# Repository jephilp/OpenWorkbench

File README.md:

# OpenWorkbench
A complete open source electrical prototyping and development toolkit. 

## The Idea
I'm currently a broke college student in Electrical Engineering. While I do have access to equipment that can meet my needs for projects, it's annoying to have to gain access to them every time I have to use them. Plus if I want to use them at home it will cost me many thousands of dollars which I don't have.

In comes the idea of the Open Workbench: I've begun gathering and developing equipment that will condense and simplify how prototyping can be done, without neededing to hunt around eBay, auctions, or buy cheap crappy equipment from Aliexpress. 

To get started I'm going to add my Logic Analyzer. It's built off of the Pi Pico Analyzer project but includes some things that I thought would be useful or nice. There's always room for improvement and I hope everyone will contribute.

## To Do:
- Create a list of basic BUILDABLE equipment.
- Create a list of BUYABLE equipment.
- Choose a mounting system (I'm thinking DIN rails).

## Current Projects:
- ATX Voltmeter
- Pi Logic Analyzer

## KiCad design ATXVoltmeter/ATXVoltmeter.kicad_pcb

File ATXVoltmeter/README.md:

# ATX VOLTMETER
Created to fufill the needs of most electrical prototyping needs. Still in progress
## Features
- +/-12 V, +/-5 V, +/-3.3 V, and Variable up to 30 V.
- Fuses on every rail
- Switches on every rail
- Current shunt on +/-12 V, +5 V and +3.3 V
- Integrated screen with monitoring

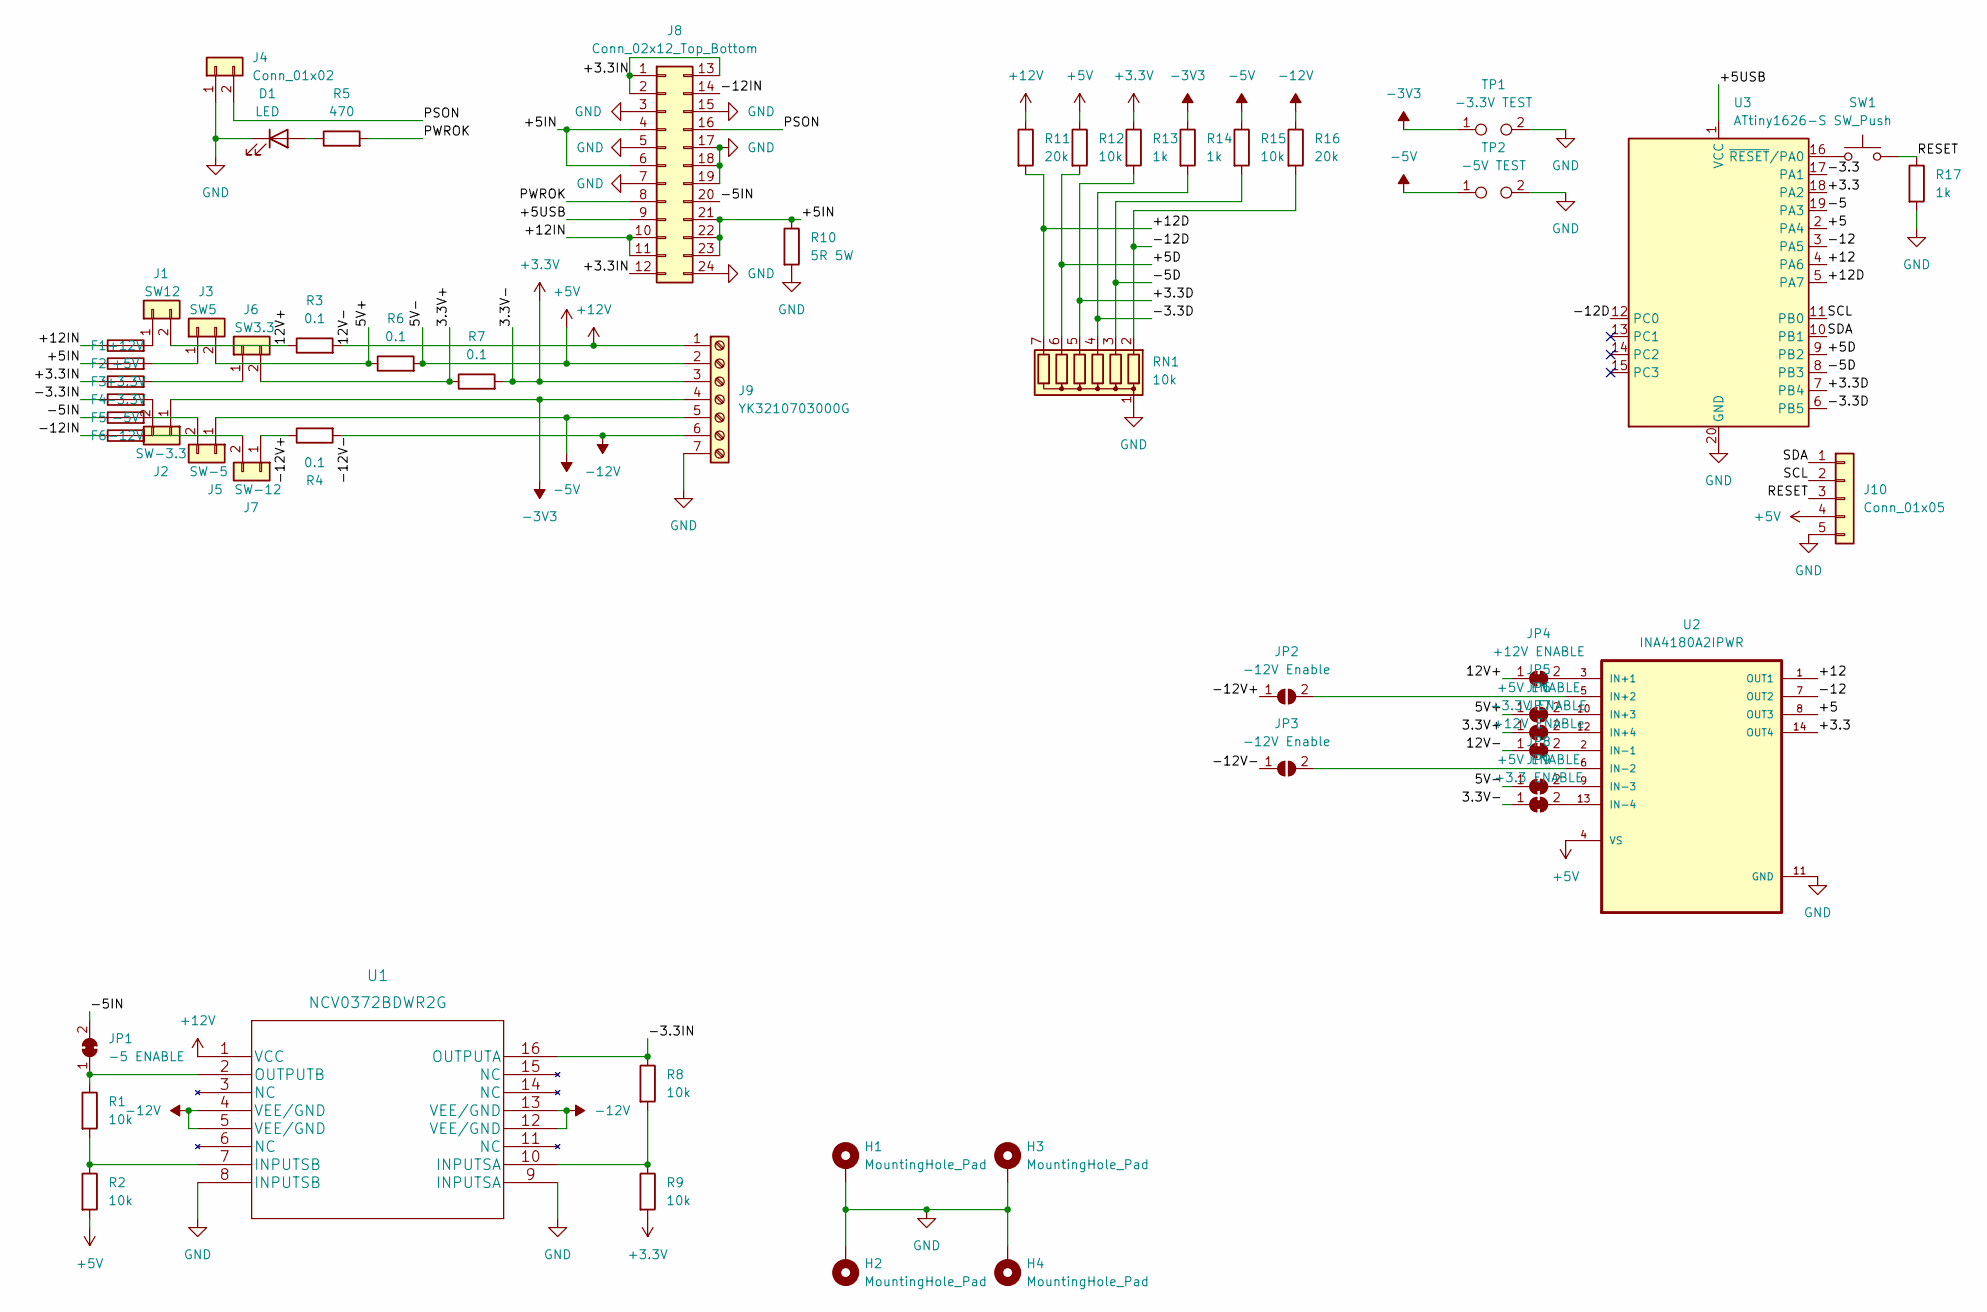
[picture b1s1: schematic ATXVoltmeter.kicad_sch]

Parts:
D1: LED; LED_D5.0mm
F1: +12V; Fuseholder_Blade_Mini_Keystone_3568
F2: +5V; Fuseholder_Blade_Mini_Keystone_3568
F3: +3.3V; Fuseholder_Blade_Mini_Keystone_3568
F4: -3.3V; Fuseholder_Blade_Mini_Keystone_3568
F5: -5V; Fuseholder_Blade_Mini_Keystone_3568
F6: -12V; Fuseholder_Blade_Mini_Keystone_3568
H1, H2, H3, H4: MountingHole_Pad; MountingHole_3.2mm_M3_DIN965_Pad
J1: SW12; AMASS_XT30U-F_1x02_P5.0mm_Vertical
J2: SW-3.3; AMASS_XT30U-F_1x02_P5.0mm_Vertical
J3: SW5; AMASS_XT30U-F_1x02_P5.0mm_Vertical
J4: Conn_01x02; PinHeader_1x02_P2.54mm_Vertical
J5: SW-5; AMASS_XT30U-F_1x02_P5.0mm_Vertical
J6: SW3.3; AMASS_XT30U-F_1x02_P5.0mm_Vertical
J7: SW-12; AMASS_XT30U-F_1x02_P5.0mm_Vertical
J8: Conn_02x12_Top_Bottom; Molex_Micro-Fit_3.0_43045-2412_2x12_P3.00mm_Vertical
J9: YK3210703000G; PhoenixContact_GMSTBVA_2,5_7-G-7,62_1x07_P7.62mm_Vertical
J10: Conn_01x05; PinSocket_1x05_P2.54mm_Horizontal
JP1: -5 ENABLE; SolderJumper-2_P1.3mm_Bridged_Pad1.0x1.5mm
JP2, JP3: -12V Enable; SolderJumper-2_P1.3mm_Open_Pad1.0x1.5mm
JP4: +12V ENABLE; SolderJumper-2_P1.3mm_Bridged_Pad1.0x1.5mm
JP5, JP8: +5V ENABLE; SolderJumper-2_P1.3mm_Bridged_Pad1.0x1.5mm
JP6: +3.3V ENABLE; SolderJumper-2_P1.3mm_Bridged_Pad1.0x1.5mm
JP7: +12V ENABLe; SolderJumper-2_P1.3mm_Bridged_Pad1.0x1.5mm
JP9: +3.3 ENABLE; SolderJumper-2_P1.3mm_Bridged_Pad1.0x1.5mm
R1, R2, R8, R9, R12, R15: 10k; R_Axial_DIN0207_L6.3mm_D2.5mm_P7.62mm_Horizontal
R3, R4, R6, R7: 0.1; R_Bare_Metal_Element_L16.3mm_W4.8mm_P15.30mm
R5: 470; R_Axial_DIN0207_L6.3mm_D2.5mm_P7.62mm_Horizontal
R10: 5R 5W; R_Axial_DIN0918_L18.0mm_D9.0mm_P22.86mm_Horizontal
R11, R16: 20k; R_Axial_DIN0207_L6.3mm_D2.5mm_P7.62mm_Horizontal
R13, R14, R17: 1k; R_Axial_DIN0207_L6.3mm_D2.5mm_P7.62mm_Horizontal
RN1: 10k; R_Array_SIP7
SW1: SW_Push; SW_PUSH_6mm
TP1: -3.3V TEST; TestPoint_2Pads_Pitch2.54mm_Drill0.8mm
TP2: -5V TEST; TestPoint_2Pads_Pitch2.54mm_Drill0.8mm
U1: NCV0372BDWR2G
U2: INA4180A2IPWR; SOP65P640X120-14N
U3: ATtiny1626-S; SOIC-20W_7.5x12.8mm_P1.27mm

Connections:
+3.3V: J9.3, JP9.1 (A), R7.2, R9.2, R13.1
+5V: J9.2, J10.4, JP8.1 (A), R2.2, R6.2, R12.1, U2.4 (VS)
+12V: J9.1, JP7.1 (A), R3.2, R11.1, U1.1 (VCC)
-3V3: J2.1, J9.4, R14.1, TP1.1
-5V: J5.1, J9.5, R15.1, TP2.1
-12V: J9.6, JP3.1 (A), R4.2, R16.1, U1.4 (VEE/GND), U1.5 (VEE/GND), U1.12 (VEE/GND), U1.13 (VEE/GND)
/3.3V+: J6.2, JP6.1 (A), R7.1
/5V+: J3.2, JP5.1 (A), R6.1
/12V+: J1.2, JP4.1 (A), R3.1
/+3.3: U2.14 (OUT4), U3.18 (PA2)
/+3.3D: R13.2, RN1.5 (R4), U3.7 (PB4)
/+3.3IN: F3.1, J8.1, J8.2, J8.12, J8.13
/+5: U2.8 (OUT3), U3.2 (PA4)
/+5D: R12.2, RN1.6 (R5), U3.9 (PB2)
/+5IN: F2.1, J8.4, J8.6, J8.21, J8.22, J8.23, R10.1
/+5USB: J8.9, U3.1 (VCC)
/+12: U2.1 (OUT1), U3.4 (PA6)
/+12D: R11.2, RN1.7 (R6), U3.5 (PA7)
/+12IN: F1.1, J8.10, J8.11
/-3.3: U3.17 (PA1)
/-3.3D: R14.2, RN1.4 (R3), U3.6 (PB5)
/-3.3IN: F4.1, R8.1, U1.16 (OUTPUTA)
/-5: U3.19 (PA3)
/-5D: R15.2, RN1.3 (R2), U3.8 (PB3)
/-5IN: F5.1, J8.20, JP1.2 (B)
/-12: U2.7 (OUT2), U3.3 (PA5)
/-12D: R16.2, RN1.2 (R1), U3.12 (PC0)
/-12IN: F6.1, J8.14
/-12V+: J7.1, JP2.1 (A), R4.1
/PSON: J4.2, J8.16
/PWROK: J8.8, R5.2
/RESET: J10.3, R17.1, SW1.2
/SCL: J10.2, U3.11 (PB0)
/SDA: J10.1, U3.10 (PB1)
GND: D1.1 (K), H1.1, H2.1, H3.1, H4.1, J4.1, J8.3, J8.5, J8.7, J8.15, J8.17, J8.18, J8.19, J8.24, J9.7, J10.5, R10.2, R17.2, RN1.1 (common), TP1.2, TP2.2, U1.8 (INPUTSB), U1.9 (INPUTSA), U2.11 (GND), U3.20 (GND)
unnamed: D1.2 (A), R5.1
unnamed: F1.2, J1.1
unnamed: F2.2, J3.1
unnamed: F3.2, J6.1
unnamed: F4.2, J2.2
unnamed: F5.2, J5.2
unnamed: F6.2, J7.2
unnamed: JP1.1 (A), R1.1, U1.2 (OUTPUTB)
unnamed: JP2.2 (B), U2.5 (IN+2)
unnamed: JP3.2 (B), U2.6 (IN-2)
unnamed: JP4.2 (B), U2.3 (IN+1)
unnamed: JP5.2 (B), U2.10 (IN+3)
unnamed: JP6.2 (B), U2.12 (IN+4)
unnamed: JP7.2 (B), U2.2 (IN-1)
unnamed: JP8.2 (B), U2.9 (IN-3)
unnamed: JP9.2 (B), U2.13 (IN-4)
unnamed: R1.2, R2.1, U1.7 (INPUTSB)
unnamed: R8.2, R9.1, U1.10 (INPUTSA)
unnamed: SW1.1, U3.16 (~RESET/PA0)

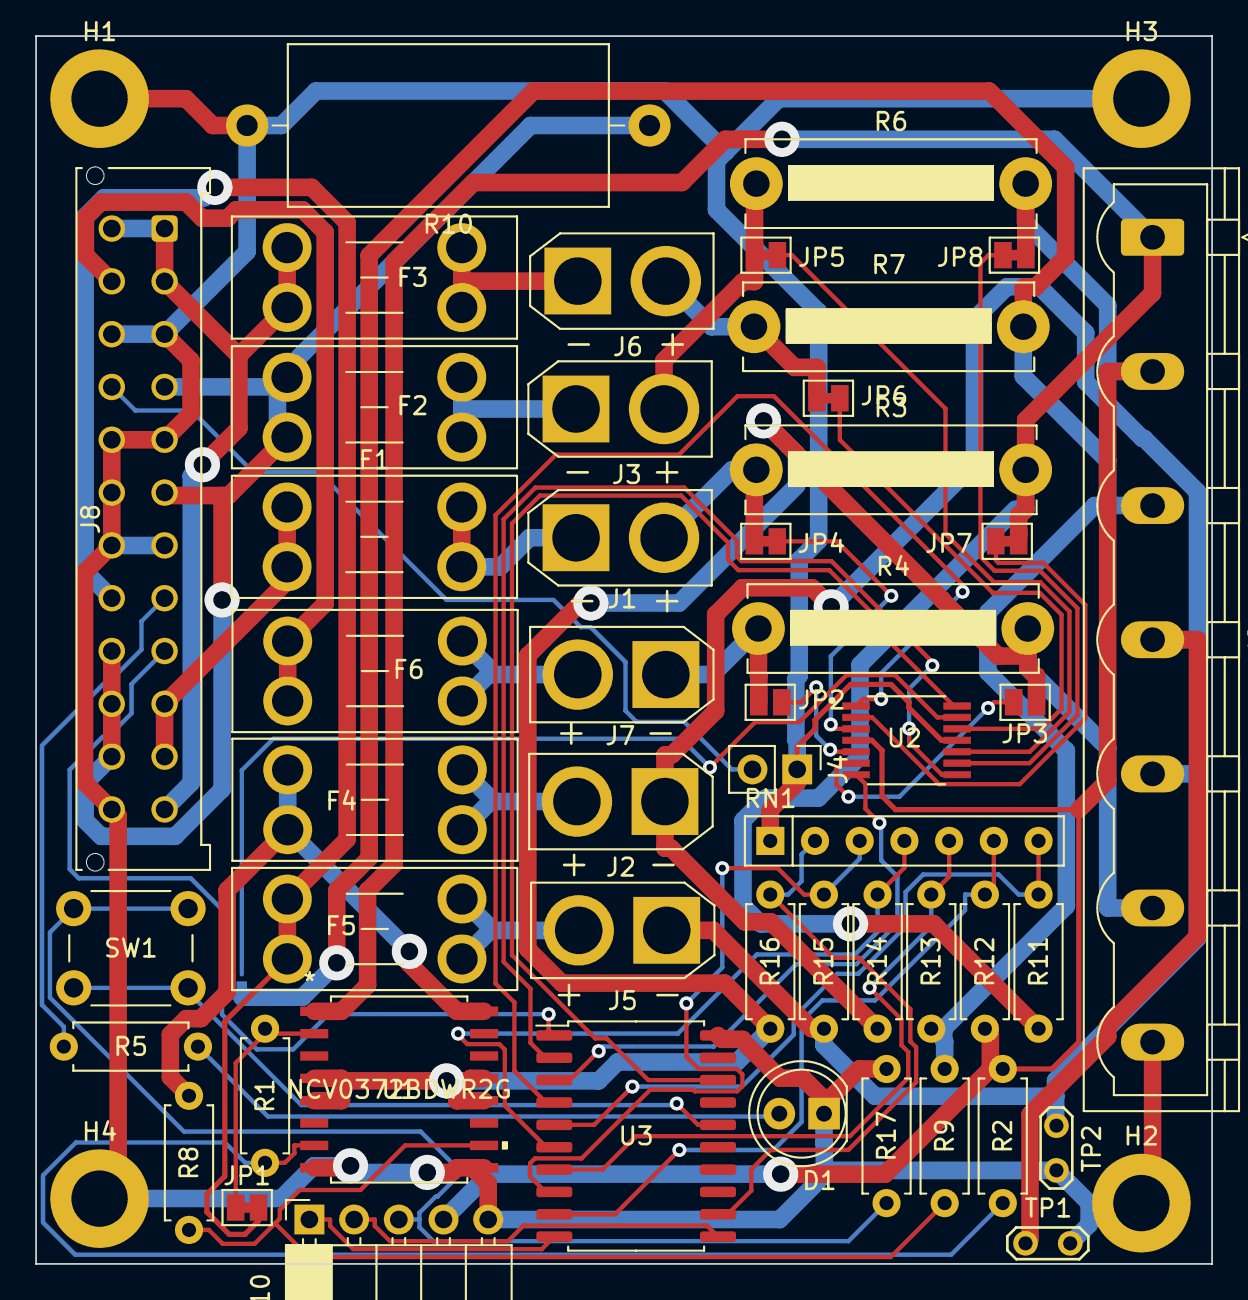
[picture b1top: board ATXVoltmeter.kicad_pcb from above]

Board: 2 copper layers, 66.8 x 69.7 mm, 54 parts (1 on the bottom side), 52 nets.

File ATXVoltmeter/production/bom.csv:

Designator,Footprint,Quantity,Value,LCSC Part #
D1,LED_D5.0mm,1,LED,
F1,Fuseholder_Blade_Mini_Keystone_3568,1,+12V,
F2,Fuseholder_Blade_Mini_Keystone_3568,1,+5V,
F3,Fuseholder_Blade_Mini_Keystone_3568,1,+3.3V,
F4,Fuseholder_Blade_Mini_Keystone_3568,1,-3.3V,
F5,Fuseholder_Blade_Mini_Keystone_3568,1,-5V,
F6,Fuseholder_Blade_Mini_Keystone_3568,1,-12V,
"H1, H2, H3, H4",MountingHole_3.2mm_M3_DIN965_Pad,4,MountingHole_Pad,
J1,AMASS_XT30U-F_1x02_P5.0mm_Vertical,1,SW12,
J16,PinSocket_1x04_P2.54mm_Horizontal,1,Conn_01x04,
J2,AMASS_XT30U-F_1x02_P5.0mm_Vertical,1,SW-3.3,
J3,AMASS_XT30U-F_1x02_P5.0mm_Vertical,1,SW5,
J4,AMASS_XT30U-F_1x02_P5.0mm_Vertical,1,SW-5,
J5,PinHeader_1x02_P2.54mm_Vertical,1,Conn_01x02,
J6,AMASS_XT30U-F_1x02_P5.0mm_Vertical,1,SW3.3,
J7,AMASS_XT30U-F_1x02_P5.0mm_Vertical,1,SW-12,
J8,Molex_Micro-Fit_3.0_43045-2412_2x12_P3.00mm_Vertical,1,Conn_02x12_Top_Bottom,
J9,"PhoenixContact_GMSTBVA_2,5_7-G-7,62_1x07_P7.62mm_Vertical",1,YK3210703000G,
"JP1, JP2",SolderJumper-2_P1.3mm_Open_Pad1.0x1.5mm,2,-12V Enable,
"JP3, JP4, JP5, JP6, JP7, JP8",SolderJumper-2_P1.3mm_Bridged_Pad1.0x1.5mm,6,SolderJumper_2_Bridged,
"R1, R10, R12, R15, R2, R9",R_Axial_DIN0207_L6.3mm_D2.5mm_P7.62mm_Horizontal,6,10k,
"R11, R16",R_Axial_DIN0207_L6.3mm_D2.5mm_P7.62mm_Horizontal,2,20k,
"R13, R14, R17, R6",R_Axial_DIN0207_L6.3mm_D2.5mm_P7.62mm_Horizontal,4,1k,
"R3, R4, R7, R8",R_Bare_Metal_Element_L16.3mm_W4.8mm_P15.30mm,4,0.1,
R5,R_Axial_DIN0207_L6.3mm_D2.5mm_P7.62mm_Horizontal,1,470,
RN1,R_Array_SIP7,1,10k,
SW1,SW_PUSH_6mm,1,SW_Push,
TP1,TestPoint_2Pads_Pitch2.54mm_Drill0.8mm,1,-3.3V TEST,
TP2,TestPoint_2Pads_Pitch2.54mm_Drill0.8mm,1,-5V TEST,
U1,NCV0372BDWR2G,1,NCV0372BDWR2G,
U2,SOP65P640X120-14N,1,INA4180A2IPWR,
U3,SOIC-20W_7.5x12.8mm_P1.27mm,1,ATtiny1626-S,

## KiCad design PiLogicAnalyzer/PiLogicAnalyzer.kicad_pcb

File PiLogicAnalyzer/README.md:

# Pi Pico Logic Analyzer
Based on the Sigrok-pico project here: https://github.com/pico-coder/sigrok-pico
## Features
- Up to 21 channels, currently limited by USB port speed
- Protection for power rails, input pins, and ground
- Configurable hardware pullups and pulldowns
- SWD Port Still accessible (5V power)
- External Reset button
- Power smoothing caps

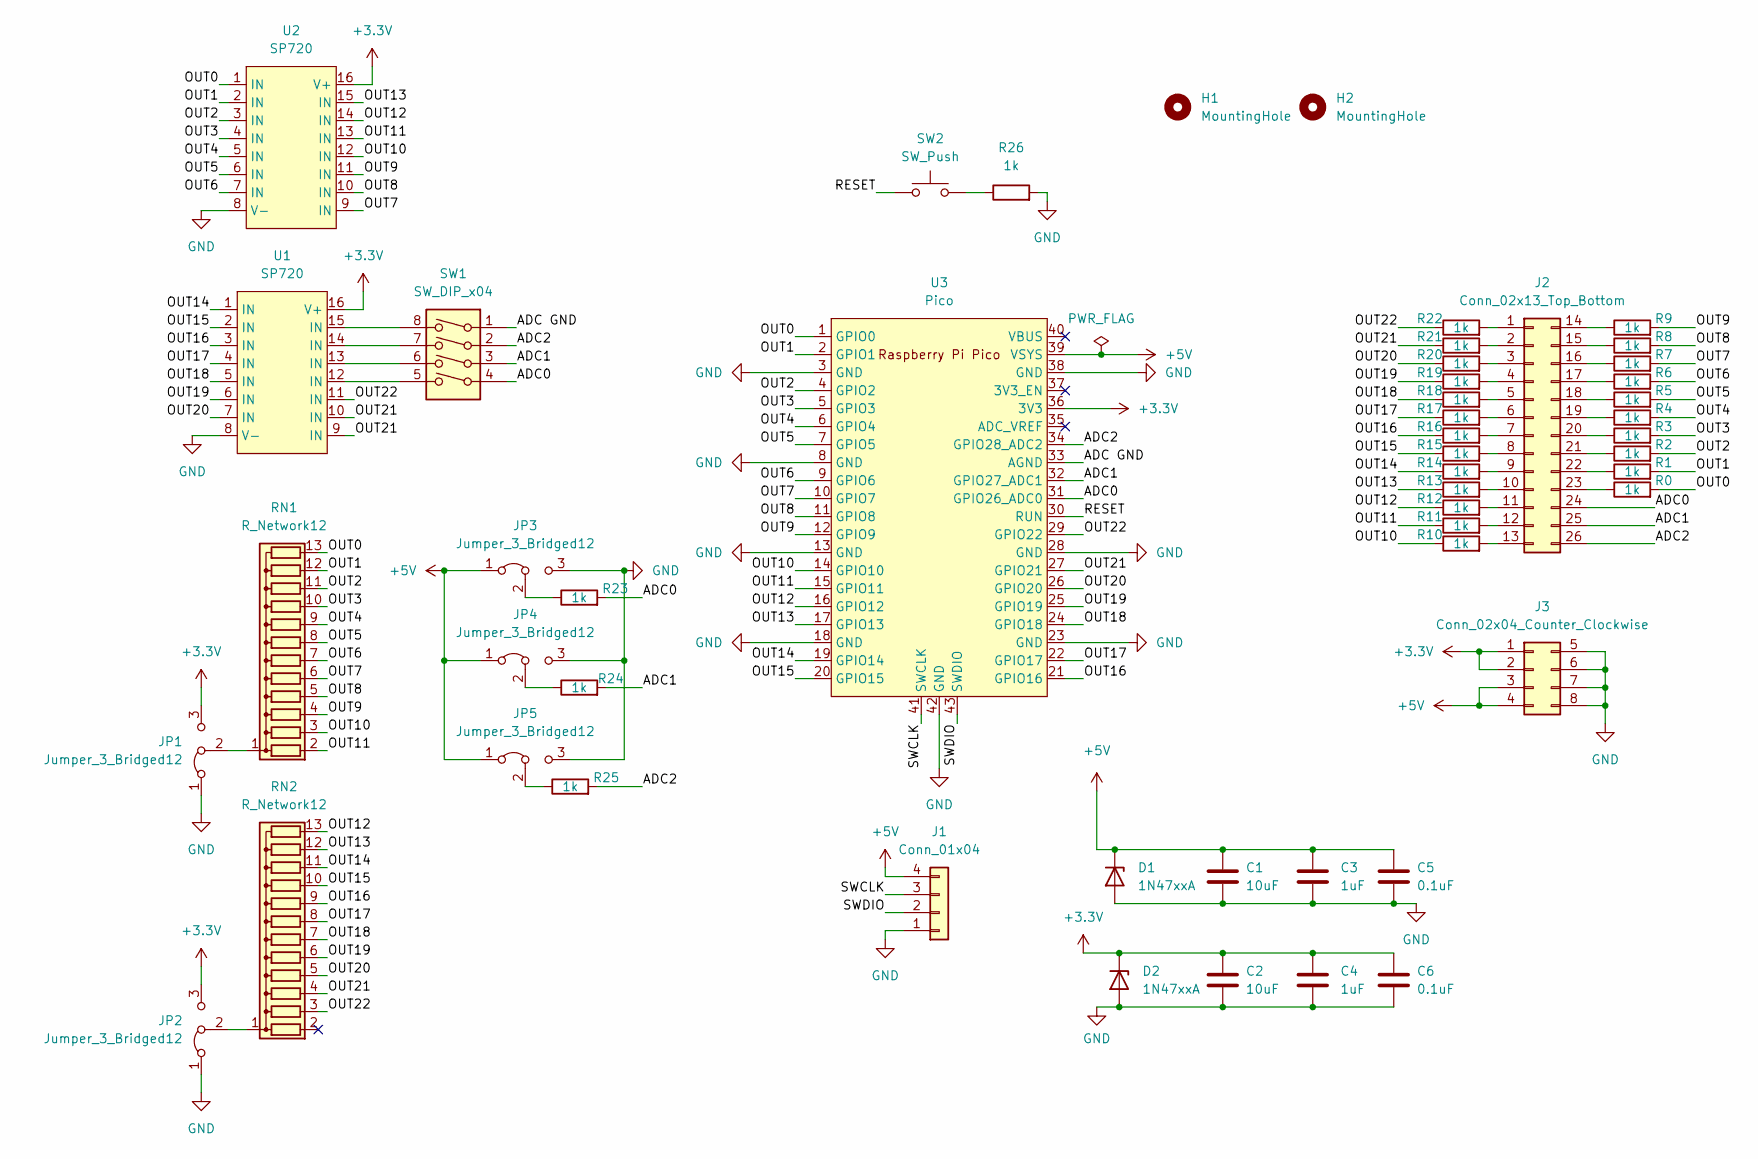
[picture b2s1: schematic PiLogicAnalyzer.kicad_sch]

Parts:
C1, C2: 10uF; C_Rect_L4.0mm_W2.5mm_P2.50mm
C3, C4: 1uF; C_Rect_L4.0mm_W2.5mm_P2.50mm
C5, C6: 0.1uF; C_Rect_L4.0mm_W2.5mm_P2.50mm
D1, D2: 1N47xxA; D_DO-41_SOD81_P10.16mm_Horizontal
H1, H2: MountingHole; MountingHole_3.2mm_M3_DIN965
J1: Conn_01x04; PinHeader_1x04_P2.54mm_Horizontal
J2: Conn_02x13_Top_Bottom; PinHeader_2x13_P2.54mm_Horizontal
J3: Conn_02x04_Counter_Clockwise; PinHeader_2x04_P2.54mm_Horizontal
JP1, JP2, JP3, JP4, JP5: Jumper_3_Bridged12; PinHeader_1x03_P2.54mm_Vertical
R0, R1, R2, R3, R4, R5, R6, R7, R8, R9, R10, R11, R12, R13, R14, R15, R16, R17, R18, R19, R20, R21, R22, R23, R24, R25, R26: 1k; R_Axial_DIN0204_L3.6mm_D1.6mm_P5.08mm_Horizontal
RN1, RN2: R_Network12; R_Array_SIP13
SW1: SW_DIP_x04; DIP-8_W7.62mm
SW2: SW_Push; SW_PUSH_6mm
U1, U2: SP720; DIP-16_W7.62mm
U3: Pico; RPi_Pico_SMD_TH

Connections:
+5V: C1.1, C3.1, C5.1, D1.1 (K), J1.4, J3.3, J3.4, JP3.1 (A), JP4.1 (A), JP5.1 (A), U3.39 (VSYS)
/ADC0: J2.24, R23.2, SW1.4, U3.31 (GPIO26_ADC0)
/ADC1: J2.25, R24.2, SW1.3, U3.32 (GPIO27_ADC1)
/ADC2: J2.26, R25.2, SW1.2, U3.34 (GPIO28_ADC2)
/ADC GND: SW1.1, U3.33 (AGND)
/OUT0: R0.2, RN1.13 (R12), U2.1 (IN), U3.1 (GPIO0)
/OUT1: R1.2, RN1.12 (R11), U2.2 (IN), U3.2 (GPIO1)
/OUT2: R2.2, RN1.11 (R10), U2.3 (IN), U3.4 (GPIO2)
/OUT3: R3.2, RN1.10 (R9), U2.4 (IN), U3.5 (GPIO3)
/OUT4: R4.2, RN1.9 (R8), U2.5 (IN), U3.6 (GPIO4)
/OUT5: R5.2, RN1.8 (R7), U2.6 (IN), U3.7 (GPIO5)
/OUT6: R6.2, RN1.7 (R6), U2.7 (IN), U3.9 (GPIO6)
/OUT7: R7.2, RN1.6 (R5), U2.9 (IN), U3.10 (GPIO7)
/OUT8: R8.2, RN1.5 (R4), U2.10 (IN), U3.11 (GPIO8)
/OUT9: R9.2, RN1.4 (R3), U2.11 (IN), U3.12 (GPIO9)
/OUT10: R10.1, RN1.3 (R2), U2.12 (IN), U3.14 (GPIO10)
/OUT11: R11.1, RN1.2 (R1), U2.13 (IN), U3.15 (GPIO11)
/OUT12: R12.1, RN2.13 (R12), U2.14 (IN), U3.16 (GPIO12)
/OUT13: R13.1, RN2.12 (R11), U2.15 (IN), U3.17 (GPIO13)
/OUT14: R14.1, RN2.11 (R10), U1.1 (IN), U3.19 (GPIO14)
/OUT15: R15.1, RN2.10 (R9), U1.2 (IN), U3.20 (GPIO15)
/OUT16: R16.1, RN2.9 (R8), U1.3 (IN), U3.21 (GPIO16)
/OUT17: R17.1, RN2.8 (R7), U1.4 (IN), U3.22 (GPIO17)
/OUT18: R18.1, RN2.7 (R6), U1.5 (IN), U3.24 (GPIO18)
/OUT19: R19.1, RN2.6 (R5), U1.6 (IN), U3.25 (GPIO19)
/OUT20: R20.1, RN2.5 (R4), U1.7 (IN), U3.26 (GPIO20)
/OUT21: R21.1, RN2.4 (R3), U1.9 (IN), U1.10 (IN), U3.27 (GPIO21)
/OUT22: R22.1, RN2.3 (R2), U1.11 (IN), U3.29 (GPIO22)
/RESET: SW2.1, U3.30 (RUN)
/SWCLK: J1.3, U3.41 (SWCLK)
/SWDIO: J1.2, U3.43 (SWDIO)
GND: C1.2, C2.2, C3.2, C4.2, C5.2, C6.2, D1.2 (A), D2.2 (A), J1.1, J3.5, J3.6, J3.7, J3.8, JP1.1 (A), JP2.1 (A), JP3.3 (B), JP4.3 (B), JP5.3 (B), R26.2, U1.8 (V-), U2.8 (V-), U3.3 (GND), U3.8 (GND), U3.13 (GND), U3.18 (GND), U3.23 (GND), U3.28 (GND), U3.38 (GND), U3.42 (GND)
unnamed: J2.1, R22.2
unnamed: J2.2, R21.2
unnamed: J2.3, R20.2
unnamed: J2.4, R19.2
unnamed: J2.14, R9.1
unnamed: J2.15, R8.1
unnamed: J2.16, R7.1
unnamed: J2.17, R6.1
unnamed: J2.18, R5.1
unnamed: J2.19, R4.1
unnamed: J2.20, R3.1
unnamed: J2.21, R2.1
unnamed: J2.22, R1.1
unnamed: J2.23, R0.1
unnamed: JP1.2 (C), RN1.1 (common)
unnamed: JP2.2 (C), RN2.1 (common)
unnamed: JP3.2 (C), R23.1
unnamed: JP4.2 (C), R24.1
unnamed: JP5.2 (C), R25.1
unnamed: J2.13, R10.2
unnamed: J2.12, R11.2
unnamed: J2.11, R12.2
unnamed: J2.10, R13.2
unnamed: J2.9, R14.2
unnamed: J2.8, R15.2
unnamed: J2.7, R16.2
unnamed: J2.6, R17.2
unnamed: J2.5, R18.2
unnamed: R26.1, SW2.2
unnamed: SW1.5, U1.12 (IN)
unnamed: SW1.6, U1.13 (IN)
unnamed: SW1.7, U1.14 (IN)
unnamed: SW1.8, U1.15 (IN)

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
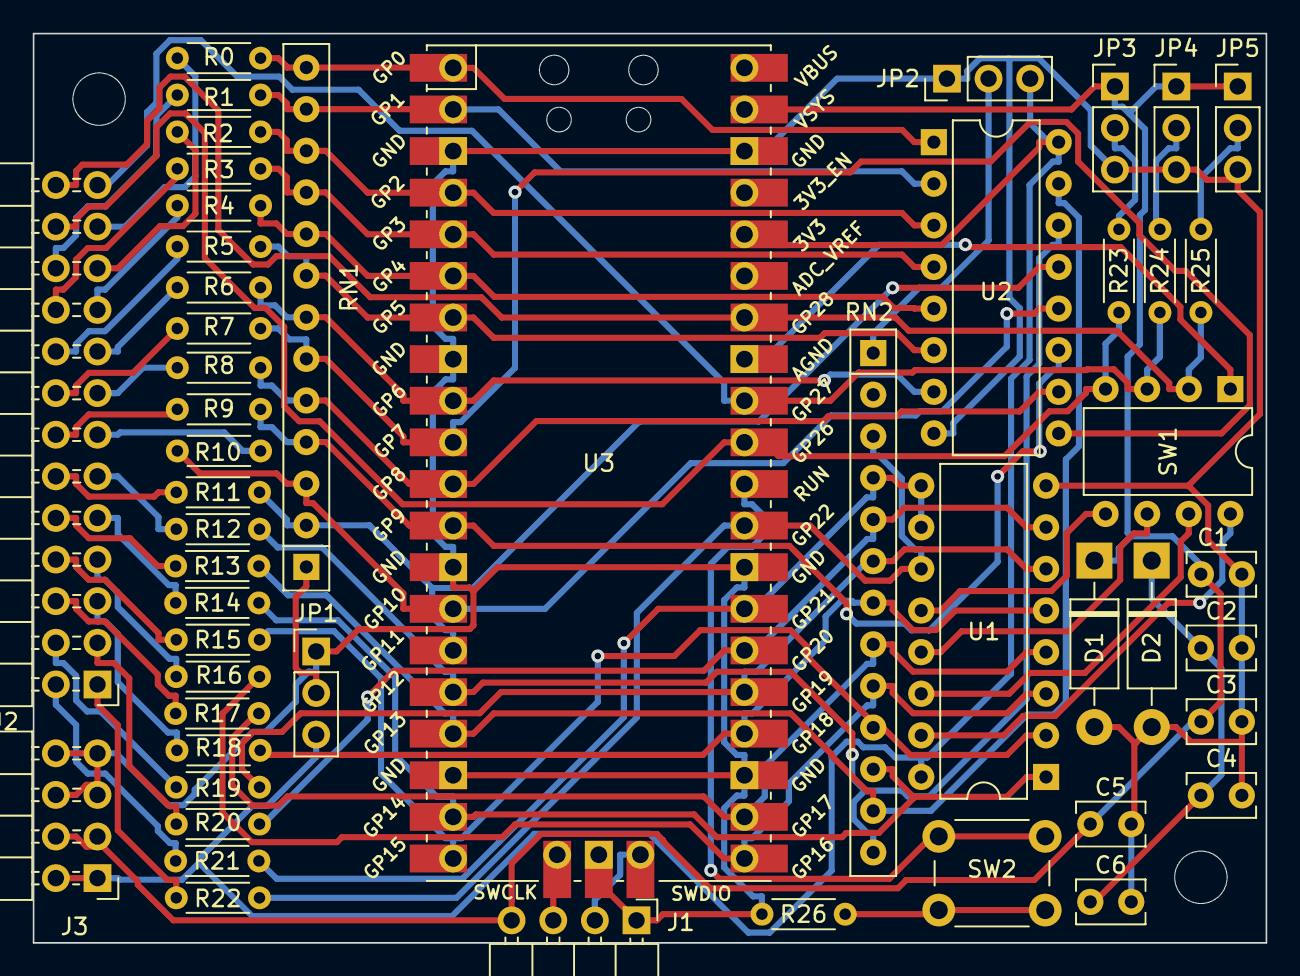
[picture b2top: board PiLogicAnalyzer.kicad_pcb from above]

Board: 2 copper layers, 75.2 x 55.5 mm, 52 parts (0 on the bottom side), 67 nets.

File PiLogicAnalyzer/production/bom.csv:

Designator,Footprint,Quantity,Value,LCSC Part #
"C1, C2",C_Rect_L4.0mm_W2.5mm_P2.50mm,2,10uF,
"C3, C4",C_Rect_L4.0mm_W2.5mm_P2.50mm,2,1uF,
"C5, C6",C_Rect_L4.0mm_W2.5mm_P2.50mm,2,0.1uF,
"D1, D2",D_DO-41_SOD81_P10.16mm_Horizontal,2,1N47xxA,
"H1, H2",MountingHole_3.2mm_M3_DIN965,2,MountingHole,
J1,PinHeader_1x04_P2.54mm_Horizontal,1,Conn_01x04,
J2,PinHeader_2x13_P2.54mm_Horizontal,1,Conn_02x13_Top_Bottom,
J3,PinHeader_2x04_P2.54mm_Horizontal,1,Conn_02x04_Counter_Clockwise,
"JP1, JP2, JP3, JP4, JP5",PinHeader_1x03_P2.54mm_Vertical,5,Jumper_3_Bridged12,
"R0, R1, R10, R11, R12, R13, R14, R15, R16, R17, R18, R19, R2, R20, R21, R22, R23, R24, R25, R26, R3, R4, R5, R6, R7, R8, R9",R_Axial_DIN0204_L3.6mm_D1.6mm_P5.08mm_Horizontal,27,1k,
"RN1, RN2",R_Array_SIP13,2,R_Network12,
SW1,DIP-8_W7.62mm,1,SW_DIP_x04,
SW2,SW_PUSH_6mm,1,SW_Push,
"U1, U2",DIP-16_W7.62mm,2,SP720,
U3,RPi_Pico_SMD_TH,1,Pico,

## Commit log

2023-03-27 Update README.md
    Created the basic outline, more to come!
2023-04-17 Added the ATX Voltmeter
2023-04-17 Added PiLogicAnalyzer
2023-04-17 Removed nested folder
